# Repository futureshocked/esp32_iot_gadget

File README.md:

# ESP32 Project: Make an IoT Gadget

This is the repository for the course ESP32 Make an IoT Gadget, from Tech Explorations.

You can find information about this course at https://techexplorations.com/product/esp32iot/

But, here's a summary:

In this course, you will learn how to make an IoT gadget.

You'll use the knowledge you acquired in ESP32 For Busy People.

You'll learn new knowledge so that you can integrate new components and tools.

This course is action-packed, but here are two highlights:

1. You'll use PlatformIO, a fully-featured, modern development environment, running inside Microsoft Visual Studio Code, an excellent graphical programming editor, in the place of the Arduino IDE. Both PlatformIO and MS Code are free applications, and with them, you'll be able to create applications that can take advantage of the capabilities of the ESP32.
2. The gadget that you'll create in this course will make use of three Cloud-based platforms: AdafruitIO, If This Then That, and Google Assistant, to implement modern IoT capabilities.

You can find the details about the objectives and the curriculum of this course in the free lectures in the first section.

As always, the course follows the familiar Tech Explorations format, which includes all schematic wiring diagrams and demo sketches, a logical course structure, high-quality video and audio, and thoughtful and calm delivery. In this course, you can also download the complete PlatformIO project file, which also includes every single Git commit I have made during the recording of the lectures.

Learn more at https://techexplorations.com/product/esp32iot/

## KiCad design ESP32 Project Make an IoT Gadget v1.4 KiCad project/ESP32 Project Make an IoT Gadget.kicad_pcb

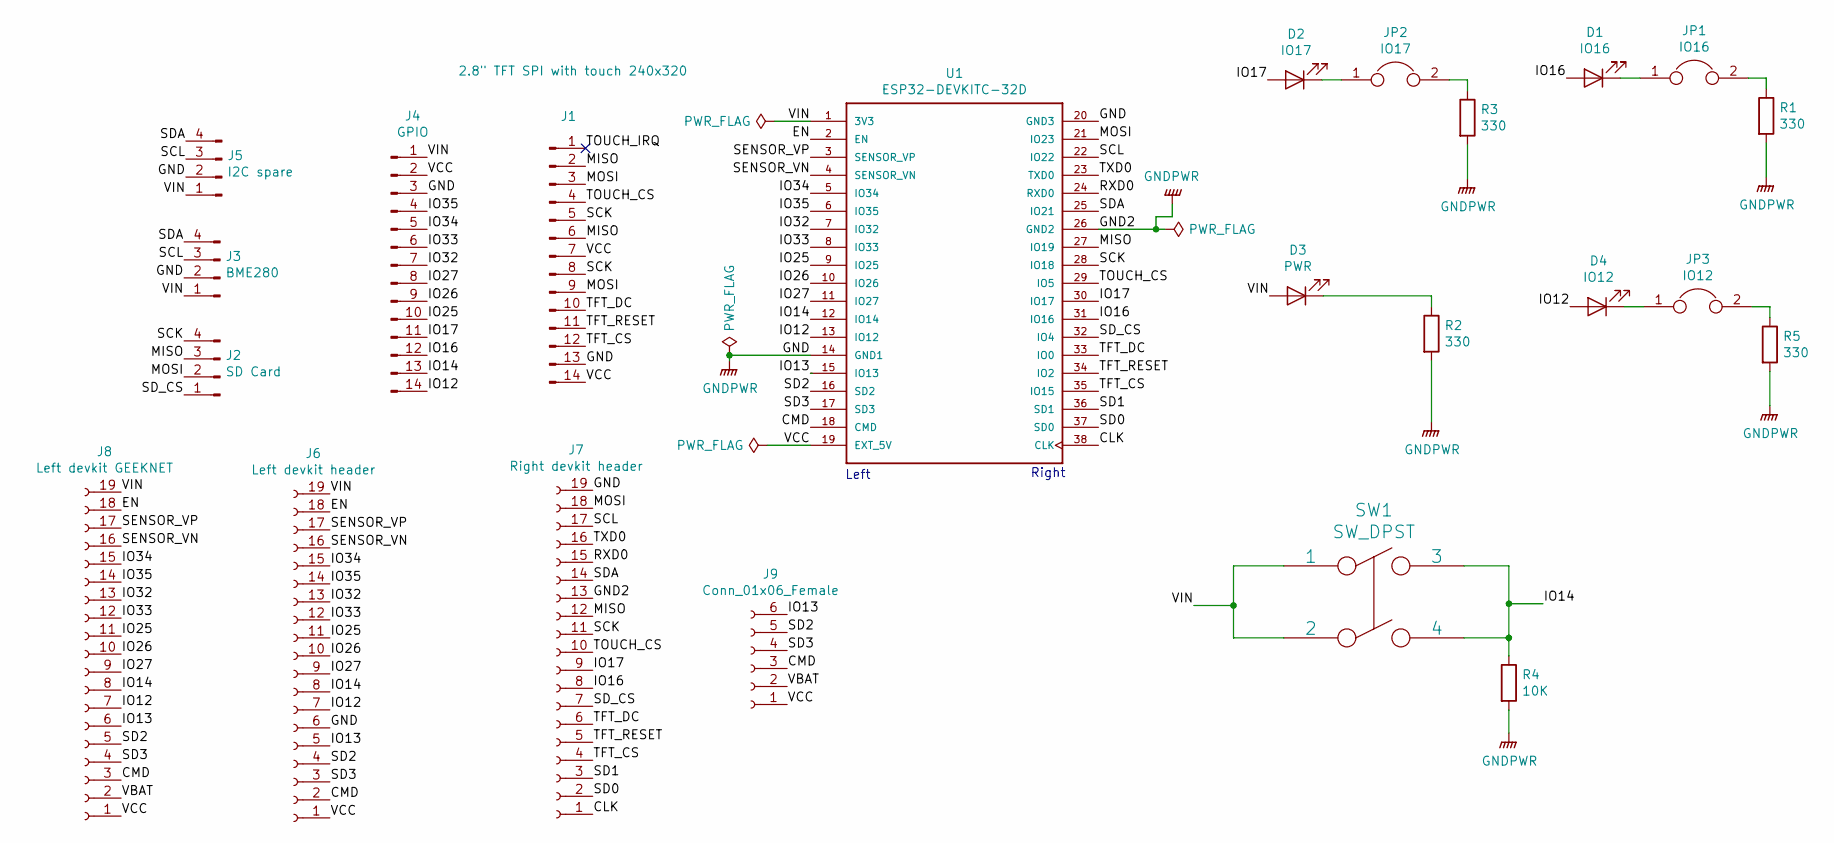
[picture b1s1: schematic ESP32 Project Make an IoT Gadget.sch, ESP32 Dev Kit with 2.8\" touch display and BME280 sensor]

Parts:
D1: IO16; LED_0805_2012Metric_Pad1.15x1.40mm_HandSolder
D2: IO17; LED_0805_2012Metric_Pad1.15x1.40mm_HandSolder
D3: PWR; LED_0805_2012Metric_Pad1.15x1.40mm_HandSolder
D4: IO12; LED_0805_2012Metric_Pad1.15x1.40mm_HandSolder
J1: 2.8\" TFT SPI with touch 240x320; PinHeader_1x14_P2.54mm_Vertical
J2: SD Card; PinHeader_1x04_P2.54mm_Vertical
J3: BME280; PinHeader_1x04_P2.54mm_Vertical
J4: GPIO; PinHeader_1x14_P2.54mm_Vertical
J5: I2C spare; PinHeader_1x04_P2.54mm_Vertical
J6: Left devkit header; PinSocket_1x19_P2.54mm_Vertical
J7: Right devkit header; PinSocket_1x19_P2.54mm_Vertical
J8: Left devkit GEEKNET; PinSocket_1x19_P2.54mm_Vertical
J9: Conn_01x06_Female; PinHeader_1x06_P2.54mm_Vertical
JP1: IO16; PinHeader_1x02_P2.54mm_Vertical
JP2: IO17; PinHeader_1x02_P2.54mm_Vertical
JP3: IO12; PinHeader_1x02_P2.54mm_Vertical
R1, R2, R3, R5: 330; R_0805_2012Metric_Pad1.15x1.40mm_HandSolder
R4: 10K; R_0805_2012Metric_Pad1.15x1.40mm_HandSolder
SW1: SW_DPST; SW_PUSHBUTTON_PTH_PD
U1: ESP32-DEVKITC-32D; MODULE_ESP32-DEVKITC_PD

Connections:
/CLK: J7.1, U1.38 (CLK)
/CMD: J6.2, J8.3, J9.3, U1.18 (CMD)
/EN: J6.18, J8.18, U1.2 (EN)
/IO12: D4.2 (A), J4.14, J6.7, J8.7, U1.13 (IO12)
/IO13: J6.5, J8.6, J9.6, U1.15 (IO13)
/IO14: J4.13, J6.8, J8.8, R4.1, SW1.3, SW1.4, U1.12 (IO14)
/IO16: D1.2 (A), J4.12, J7.8, U1.31 (IO16)
/IO17: D2.2 (A), J4.11, J7.9, U1.30 (IO17)
/IO25: J4.10, J6.11, J8.11, U1.9 (IO25)
/IO26: J4.9, J6.10, J8.10, U1.10 (IO26)
/IO27: J4.8, J6.9, J8.9, U1.11 (IO27)
/IO32: J4.7, J6.13, J8.13, U1.7 (IO32)
/IO33: J4.6, J6.12, J8.12, U1.8 (IO33)
/IO34: J4.5, J6.15, J8.15, U1.5 (IO34)
/IO35: J4.4, J6.14, J8.14, U1.6 (IO35)
/MISO: J1.2, J1.6, J2.3, J7.12, U1.27 (IO19)
/MOSI: J1.3, J1.9, J2.2, J7.18, U1.21 (IO23)
/RXD0: J7.15, U1.24 (RXD0)
/SCK: J1.5, J1.8, J2.4, J7.11, U1.28 (IO18)
/SCL: J3.3, J5.3, J7.17, U1.22 (IO22)
/SD0: J7.2, U1.37 (SD0)
/SD1: J7.3, U1.36 (SD1)
/SD2: J6.4, J8.5, J9.5, U1.16 (SD2)
/SD3: J6.3, J8.4, J9.4, U1.17 (SD3)
/SDA: J3.4, J5.4, J7.14, U1.25 (IO21)
/SD_CS: J2.1, J7.7, U1.32 (IO4)
/SENSOR_VN: J6.16, J8.16, U1.4 (SENSOR_VN)
/SENSOR_VP: J6.17, J8.17, U1.3 (SENSOR_VP)
/TFT_CS: J1.12, J7.4, U1.35 (IO15)
/TFT_DC: J1.10, J7.6, U1.33 (IO0)
/TFT_RESET: J1.11, J7.5, U1.34 (IO2)
/TOUCH_CS: J1.4, J7.10, U1.29 (IO5)
/TOUCH_IRQ: J1.1
/TXD0: J7.16, U1.23 (TXD0)
/VBAT: J8.2, J9.2
/VCC: J1.7, J1.14, J4.2, J6.1, J8.1, J9.1, U1.19 (EXT_5V)
/VIN: D3.2 (A), J3.1, J4.1, J5.1, J6.19, J8.19, SW1.1, SW1.2, U1.1 (3V3)
GNDPWR: J1.13, J3.2, J4.3, J5.2, J6.6, J7.13, J7.19, R1.2, R2.2, R3.2, R4.2, R5.2, U1.14 (GND1), U1.20 (GND3), U1.26 (GND2)
unnamed: D1.1 (K), JP1.1
unnamed: D2.1 (K), JP2.1
unnamed: D3.1 (K), R2.1
unnamed: D4.1 (K), JP3.1
unnamed: JP1.2, R1.1
unnamed: JP2.2, R3.1
unnamed: JP3.2, R5.1

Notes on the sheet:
Left
Right

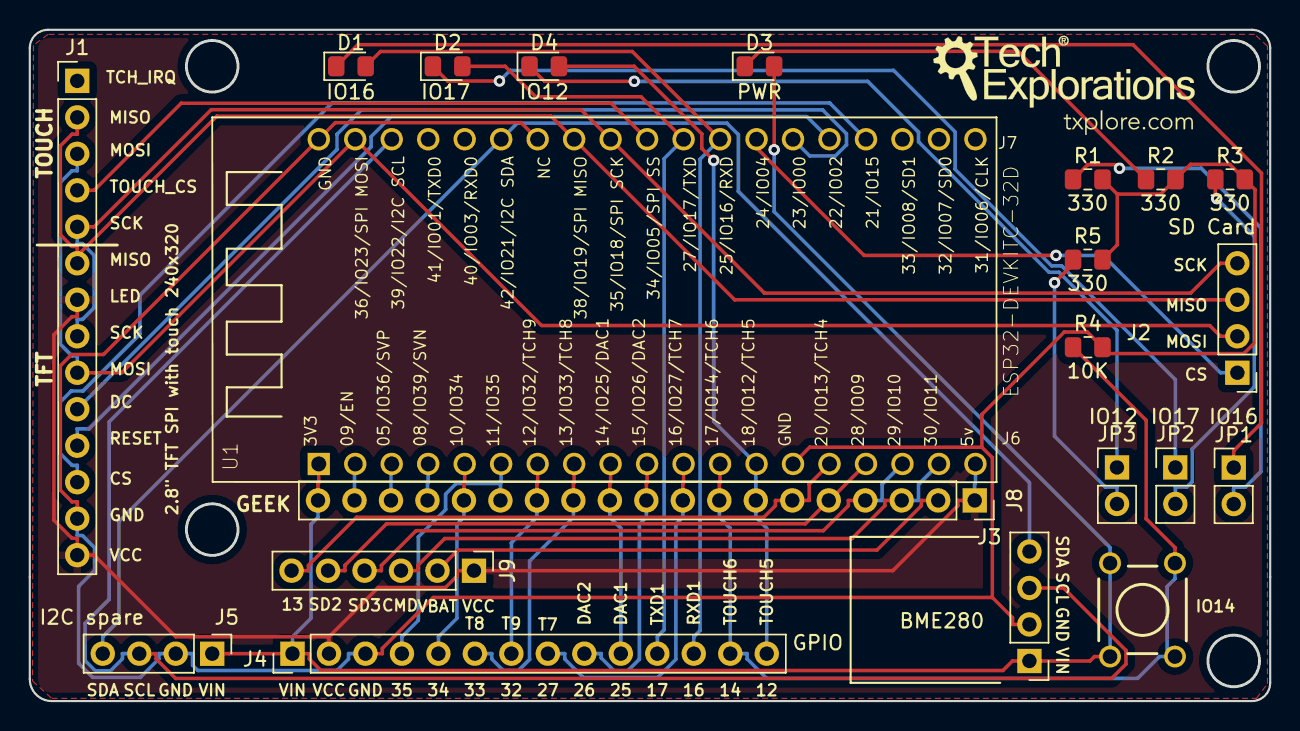
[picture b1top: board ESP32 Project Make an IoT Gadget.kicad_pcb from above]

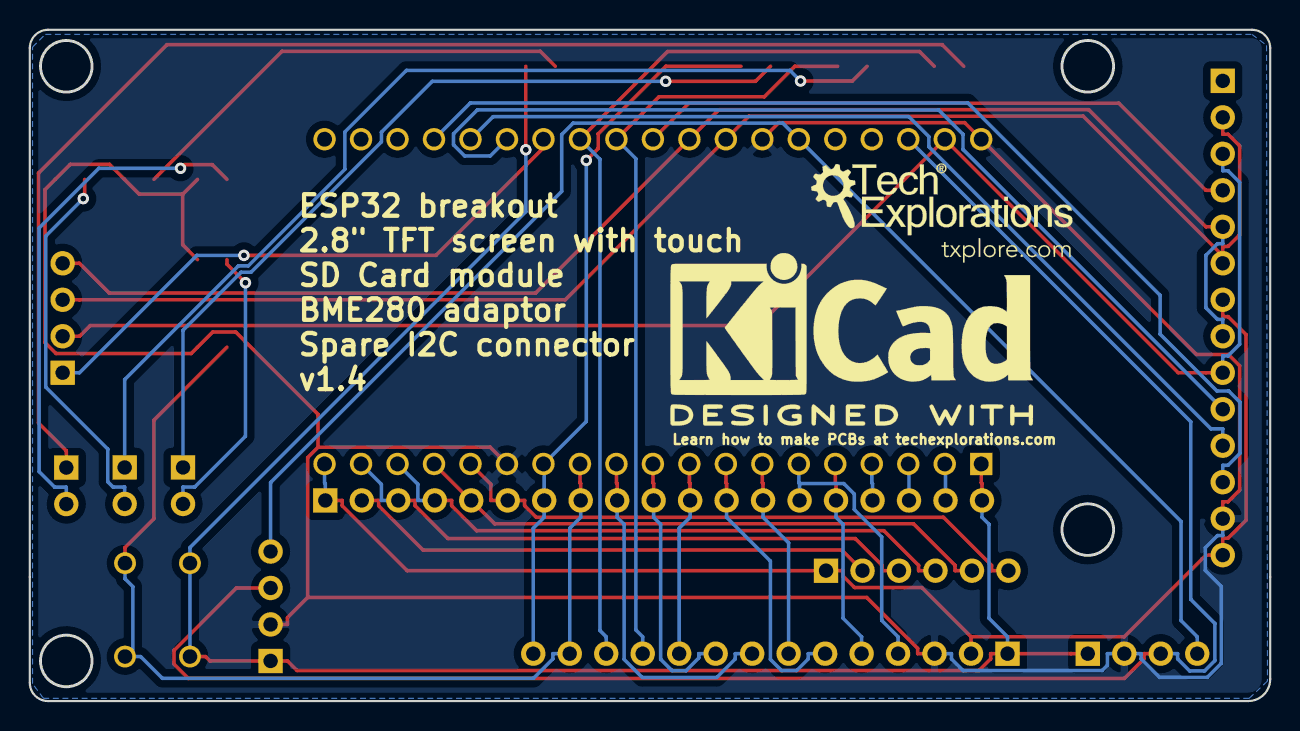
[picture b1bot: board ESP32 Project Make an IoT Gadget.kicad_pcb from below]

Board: 2 copper layers, 86.3 x 46.7 mm, 24 parts (2 on the bottom side), 39 nets.

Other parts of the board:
G1, G2: LOGO; TE_LOGO_URL_v2
REF1: KiCad-Logo2_12mm_SilkScreen

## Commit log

2019-06-17 First commit.
2019-06-17 Added PlatformIO project, src only.
2019-06-17 Added PlatformIO project, final version with src only (the full project is downloadable as a ZIP archive.
2019-06-17 Added course information and link
2022-01-16 Improved reliability with semaphores.
2022-01-16 Improved reliability using semaphores.
2022-01-30 Added Task Watchdog Timer and cloud logger
